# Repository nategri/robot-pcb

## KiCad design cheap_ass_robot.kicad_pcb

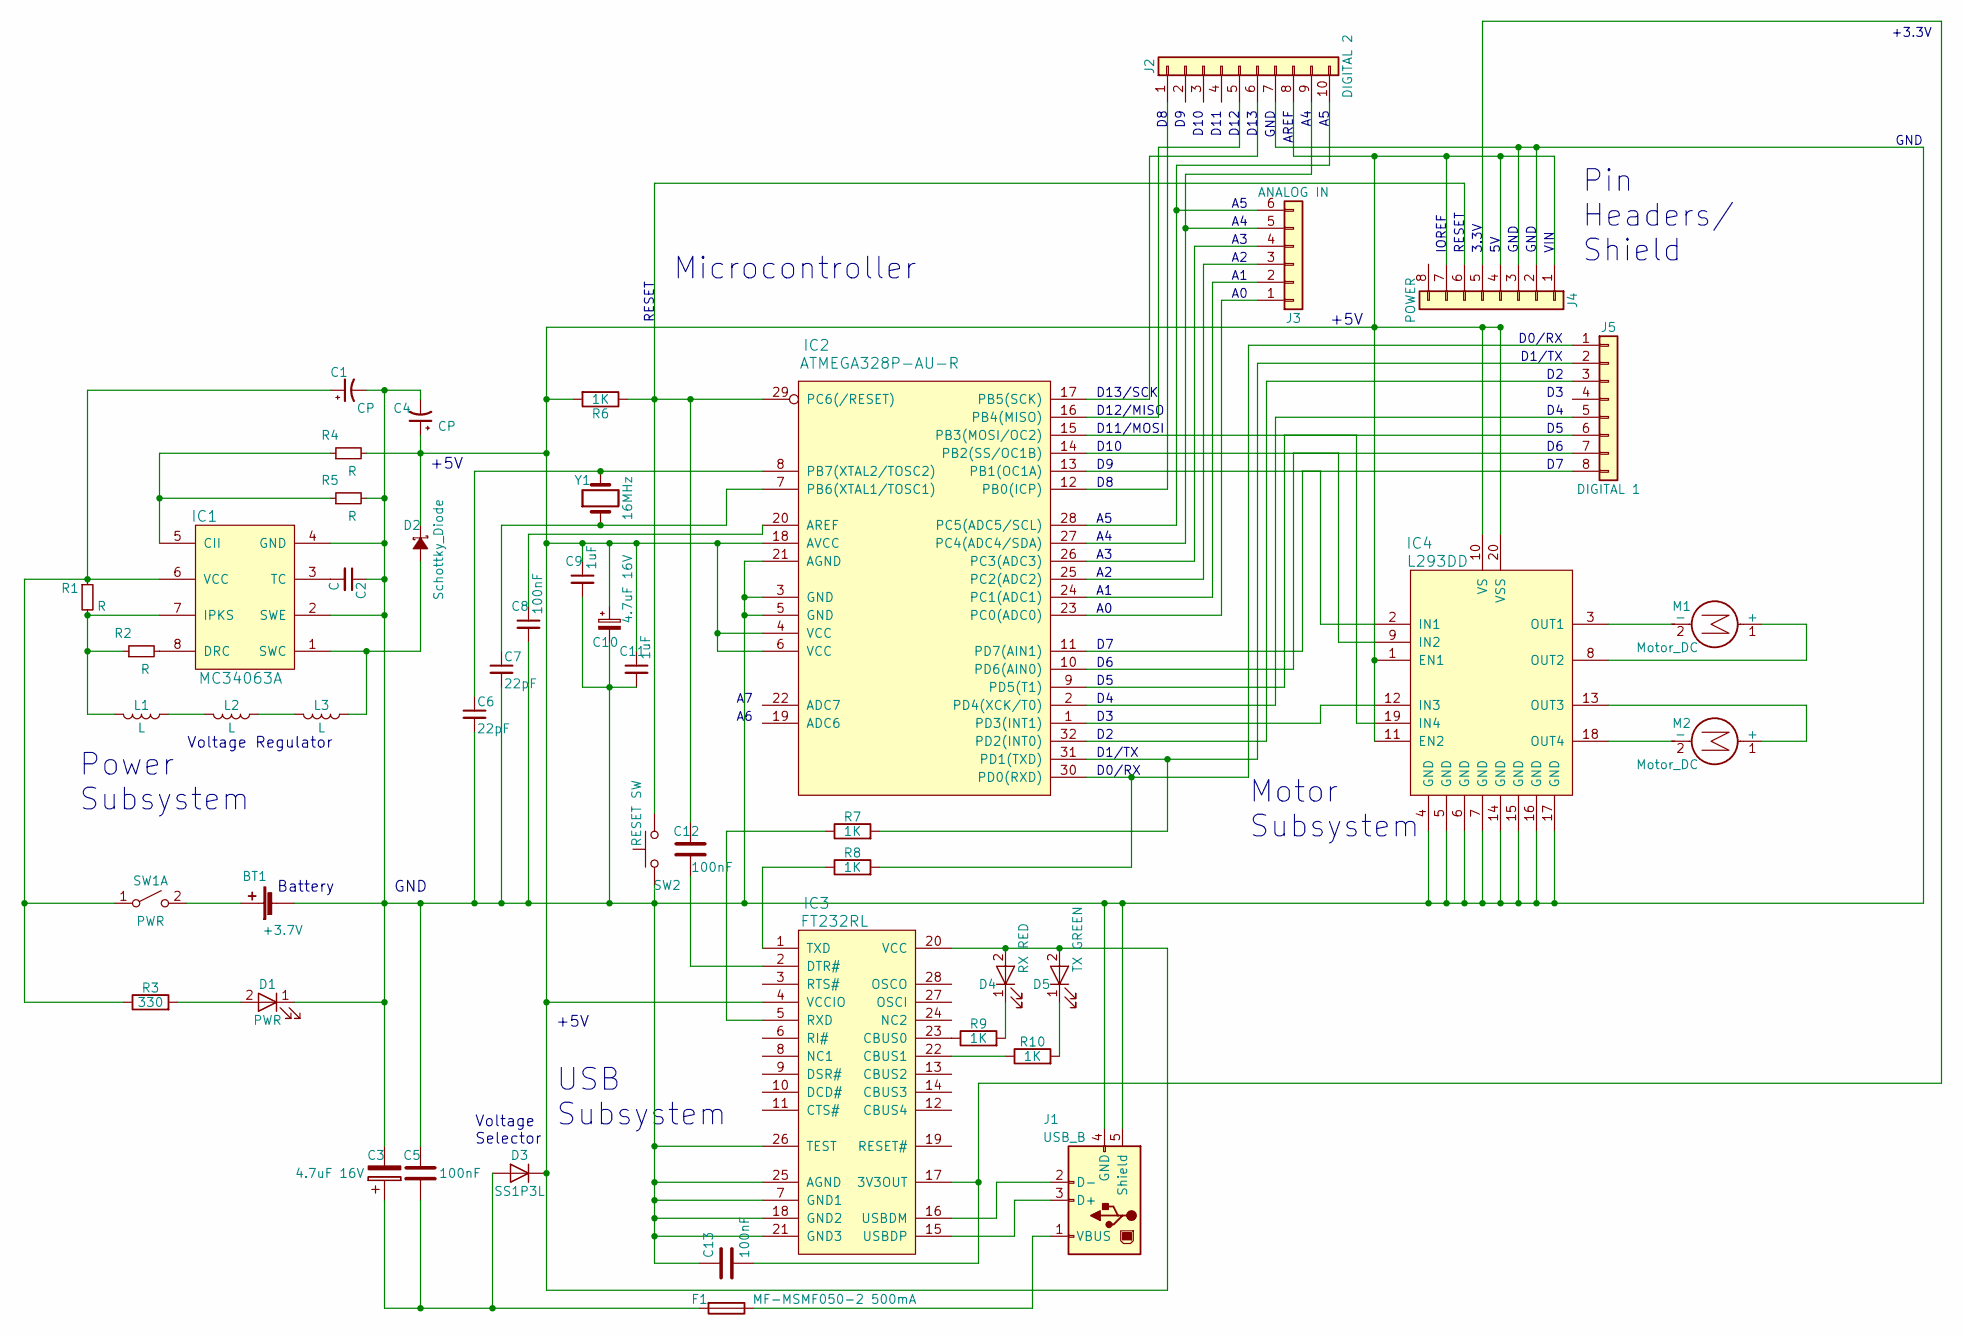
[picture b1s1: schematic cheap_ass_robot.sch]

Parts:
BT1: +3.7V; JST_PH_S2B-PH-SM4-TB_02x2.00mm_Angled
C1: CP; CP_Elec_4x5.7
C2: C; C_0805
C3, C10: 4.7uF 16V; CP_Elec_4x5.7
C4: CP; CP_Elec_6.3x7.7
C5, C8, C12, C13: 100nF; C_0805
C6, C7: 22pF; C_0805
C9, C11: 1uF; C_0805
D1: PWR; LED_0805
D2: Schottky_Diode; D_SOD-123F
D3: SS1P3L; D_SOD-123F
D4: RX RED; LED_0805
D5: TX GREEN; LED_0805
F1: MF-MSMF050-2 500mA; R_1206
IC1: MC34063A; SOIC-8_3.9x4.9mm_Pitch1.27mm
IC2: ATMEGA328P-AU-R; TQFP-32_7x7mm_Pitch0.8mm
IC3: FT232RL; SSOP-28_5.3x10.2mm_Pitch0.65mm
IC4: L293DD; SO-20_12.8x7.5mm_Pitch1.27mm
J1: USB_B
J2: DIGITAL 2; Pin_Header_Straight_1x10_Pitch2.54mm
J3: ANALOG IN; Pin_Header_Straight_1x06_Pitch2.54mm
J4: POWER; Pin_Header_Straight_1x08_Pitch2.54mm
J5: DIGITAL 1; Pin_Header_Straight_1x08_Pitch2.54mm
L1, L2, L3: L; L_0805
M1, M2: Motor_DC; PINHEAD1-2
R1, R2, R4, R5: R; R_0805
R3: 330; R_0805
R6, R7, R8, R9, R10: 1K; R_0805
SW1: PWR; PINHEAD1-3
SW2: RESET SW; SW_PUSH_6mm
Y1: 16MHz; Crystal_SMD_HC49-SD

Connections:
unnamed: BT1.1 (+), SW1.2 (B)
unnamed: BT1.2 (-), C1.2, C2.1, C3.2, C4.2, C5.1, C6.2, C7.2, C8.2, C9.2, C10.2, C11.2, C13.1, D1.1 (K), IC1.2 (SWE), IC1.4 (GND), IC2.3 (GND), IC2.5 (GND), IC2.21 (AGND), IC3.7 (GND1), IC3.18 (GND2), IC3.21 (GND3), IC3.25 (AGND), IC3.26 (TEST), IC4.4 (GND), IC4.5 (GND), IC4.6 (GND), IC4.7 (GND), IC4.14 (GND), IC4.15 (GND), IC4.16 (GND), IC4.17 (GND), J1.4 (GND), J1.5 (Shield), J2.7, J4.2, J4.3, R5.2, SW2.1
unnamed: C1.1, IC1.6 (VCC), R1.1, R3.1, SW1.1 (A)
unnamed: C2.2, IC1.3 (TC)
unnamed: C3.1, C5.2, D3.2 (A), F1.2
unnamed: C6.1, IC2.8 (PB7(XTAL2/TOSC2)), Y1.2
unnamed: C7.1, IC2.7 (PB6(XTAL1/TOSC1)), Y1.1
unnamed: C8.1, IC2.20 (AREF)
unnamed: C4.1, C9.1, C10.1, C11.1, D2.1 (K), D3.1 (K), D4.2 (A), D5.2 (A), IC2.4 (VCC), IC2.6 (VCC), IC2.18 (AVCC), IC3.4 (VCCIO), IC3.20 (VCC), IC4.1 (EN1), IC4.10 (VS), IC4.11 (EN2), IC4.20 (VSS), J2.8, J4.1, J4.4, J4.7, R4.2, R6.2
unnamed: C12.1, IC2.29 (PC6(/RESET)), J4.6, R6.1, SW2.2
unnamed: C12.2, IC3.2 (DTR#)
unnamed: C13.2, IC3.17 (3V3OUT), J4.5
unnamed: D1.2 (A), R3.2
unnamed: D2.2 (A), IC1.1 (SWC), L3.1
unnamed: D4.1 (K), R9.2
unnamed: D5.1 (K), R10.2
unnamed: F1.1, J1.1 (VBUS)
unnamed: IC1.5 (CII), R4.1, R5.1
unnamed: IC1.7 (IPKS), L1.2, R1.2, R2.1
unnamed: IC1.8 (DRC), R2.2
unnamed: IC2.1 (PD3(INT1)), IC4.12 (IN3)
unnamed: IC2.2 (PD4(XCK/T0)), J5.5
unnamed: IC2.9 (PD5(T1)), J5.6
unnamed: IC2.10 (PD6(AIN0)), J5.7
unnamed: IC2.11 (PD7(AIN1)), J5.8
unnamed: IC2.12 (PB0(ICP)), J2.1
unnamed: IC2.13 (PB1(OC1A)), IC4.2 (IN1)
unnamed: IC2.14 (PB2(SS/OC1B)), IC4.9 (IN2)
unnamed: IC2.15 (PB3(MOSI/OC2)), IC4.19 (IN4)
unnamed: IC2.16 (PB4(MISO)), J2.5
unnamed: IC2.17 (PB5(SCK)), J2.6
unnamed: IC2.23 (PC0(ADC0)), J3.1
unnamed: IC2.24 (PC1(ADC1)), J3.2
unnamed: IC2.25 (PC2(ADC2)), J3.3
unnamed: IC2.26 (PC3(ADC3)), J3.4
unnamed: IC2.27 (PC4(ADC4/SDA)), J2.9, J3.5
unnamed: IC2.28 (PC5(ADC5/SCL)), J2.10, J3.6
unnamed: IC2.30 (PD0(RXD)), J5.1, R8.2
unnamed: IC2.31 (PD1(TXD)), J5.2, R7.2
unnamed: IC2.32 (PD2(INT0)), J5.3
unnamed: IC3.1 (TXD), R8.1
unnamed: IC3.5 (RXD), R7.1
unnamed: IC3.15 (USBDP), J1.3 (D+)
unnamed: IC3.16 (USBDM), J1.2 (D-)
unnamed: IC3.22 (CBUS1), R10.1
unnamed: IC3.23 (CBUS0), R9.1
unnamed: IC4.3 (OUT1), M1.2 (-)
unnamed: IC4.8 (OUT2), M1.1 (+)
unnamed: IC4.13 (OUT3), M2.1 (+)
unnamed: IC4.18 (OUT4), M2.2 (-)
unnamed: L1.1, L2.2
unnamed: L2.1, L3.2

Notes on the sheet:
D0/RX
D1/TX
D10
D11/MOSI
D12/MISO
D13/SCK
RESET
Voltage Regulator
Battery
+5V
GND
Power Subsystem
USB Subsystem
Microcontroller
Pin Headers/ Shield
Motor Subsystem
Voltage Selector
D11
D12
D13
AREF
VIN
3.3V
IOREF
+3.3V

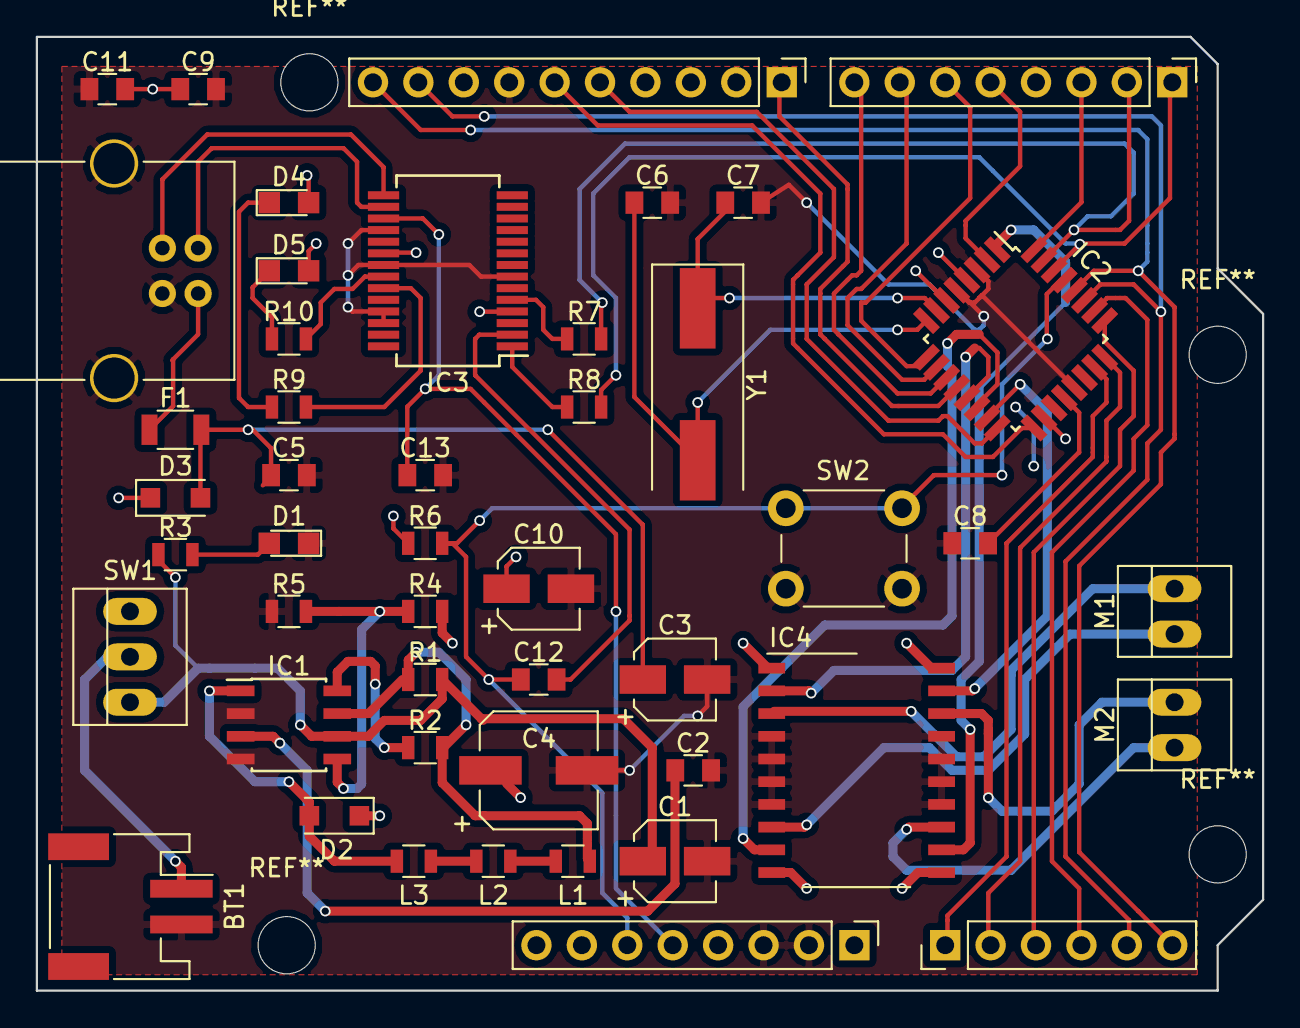
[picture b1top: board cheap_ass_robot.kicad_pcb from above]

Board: 2 copper layers, 68.6 x 53.3 mm, 47 parts (0 on the bottom side), 52 nets.

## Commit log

2018-09-15 fixed diagram level electrical issues and added caps from xtal to gnd
2018-09-28 will probably be revision alpha-1
2019-04-14 sync; most recent change was fixing missed connection to ground on ftdi chip
2019-04-17 widen traces on on segments likely to pull larger currents
2019-04-17 final save before export upload to oshpark
2019-04-17 not even sure how this got modified but okay
2019-05-11 all out war against heat
